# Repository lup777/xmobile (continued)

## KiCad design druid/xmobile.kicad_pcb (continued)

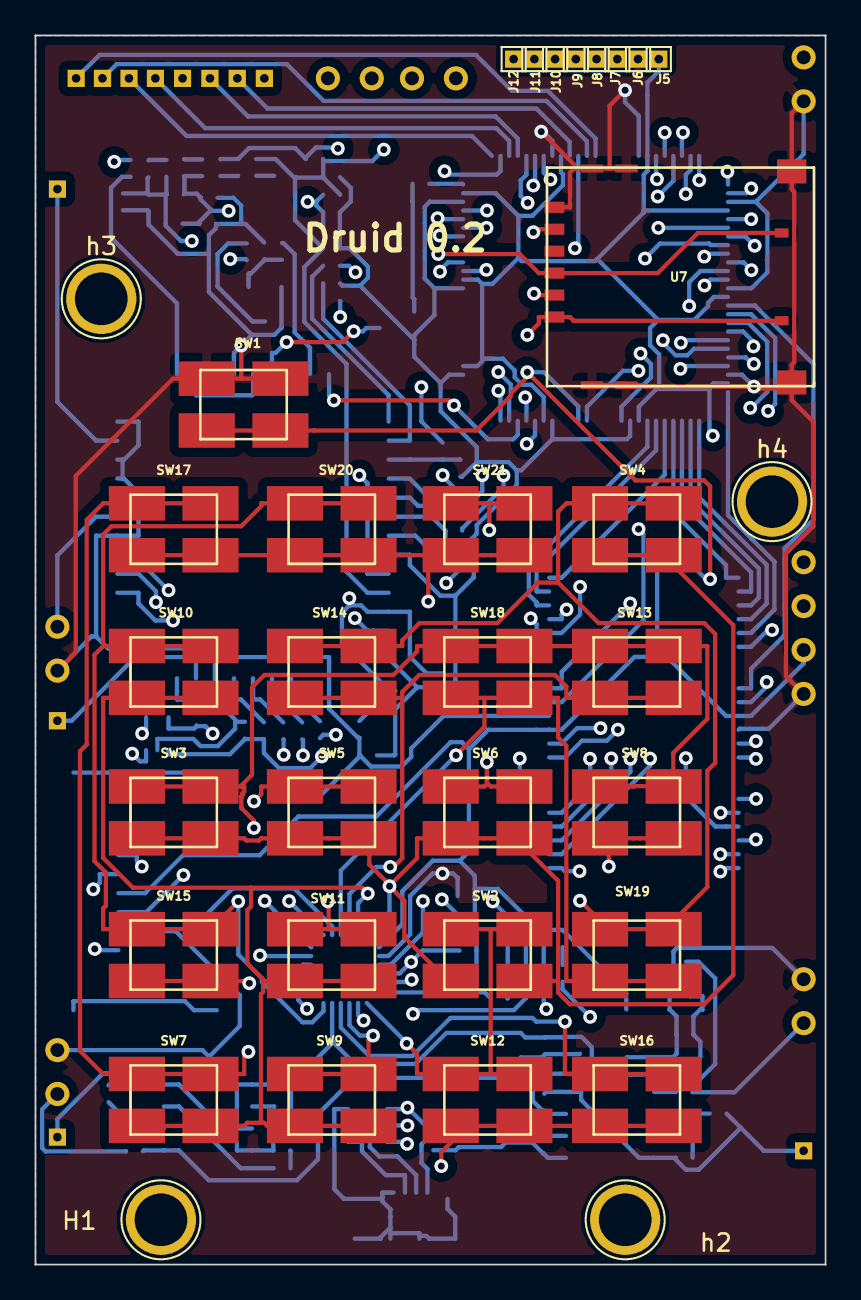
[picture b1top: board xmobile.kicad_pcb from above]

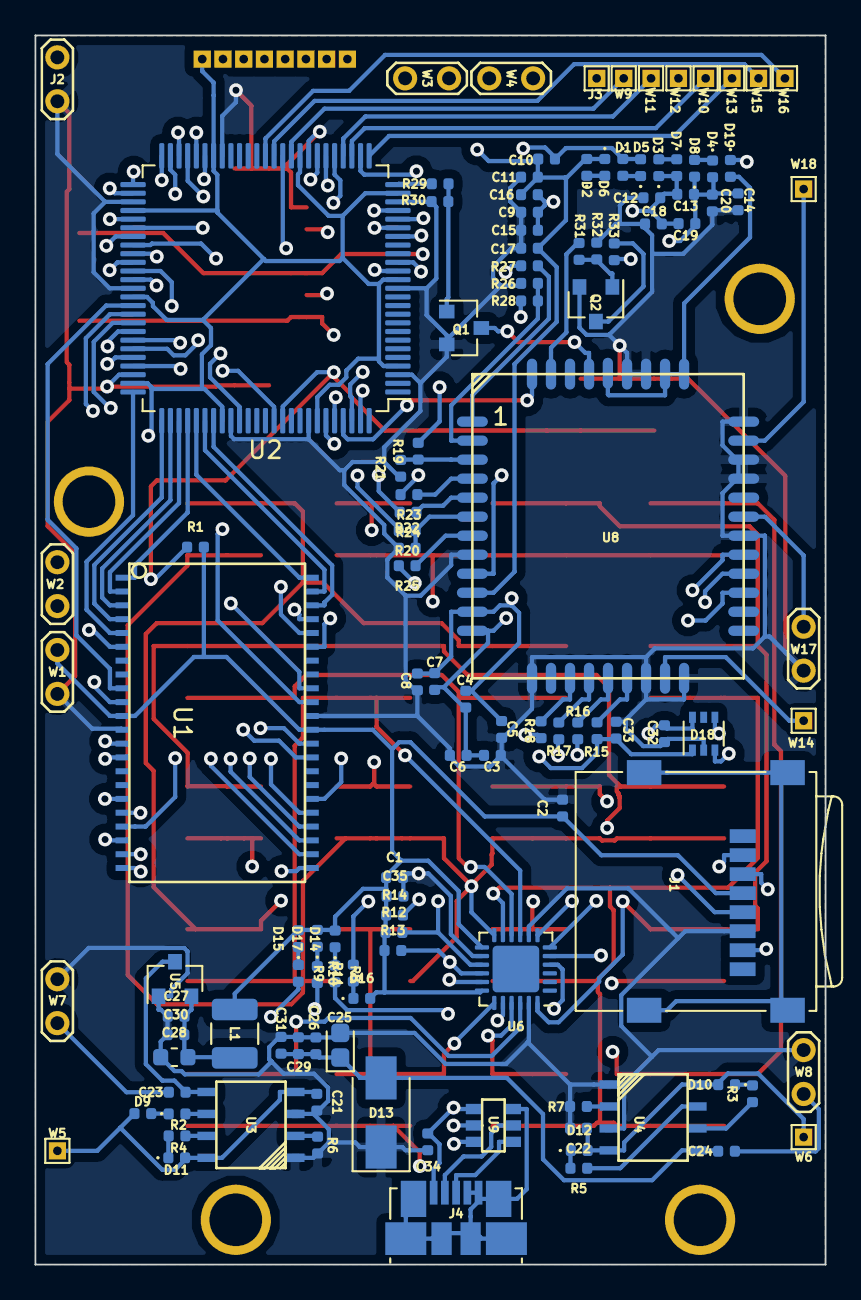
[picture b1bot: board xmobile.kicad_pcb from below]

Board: 4 copper layers, 45.7 x 71.1 mm, 154 parts (120 on the bottom side), 133 nets.

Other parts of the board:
H1: 1pin
J5, J6, J7, J8, J9, J10, J11, J12: EPD_1; TestPoint_THTPad_1.0x1.0mm_Drill0.5mm
h2, h3, h4: 1pin

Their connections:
3.3V: J5.1; also elsewhere on the board
/EPD_BUSY: J12.1; also elsewhere on the board
/EPD_CLK: J8.1; also elsewhere on the board
/EPD_CS: J9.1; also elsewhere on the board
/EPD_DC: J10.1; also elsewhere on the board
/EPD_DIN: J7.1; also elsewhere on the board
/EPD_RST: J11.1; also elsewhere on the board
GND: J6.1; also elsewhere on the board

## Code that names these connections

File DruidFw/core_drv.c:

// core_drv.c
#include <avr/io.h>

#include "global.h"

#include "core_drv.h"

void WriteEBI(uint32_t Address, uint8_t Val);
uint8_t ReadEBI(uint32_t Address);
void sram_read_enable(void);
void sram_write_enable(void);

inline void clk_init(void) {
    //OSC_PLLCTRL = 0x16;  // 2 * 16 = 32MGz
  OSC_CTRL = OSC_RC32MEN_bm;

  while( !( OSC_STATUS & OSC_RC32MRDY_bm ) ); // waite while 32MGXz osc ready

  CCP = CCP_IOREG_gc;
  CLK_CTRL = CLK_SCLKSEL_RC32M_gc;
}

void int_init(void) {
  //clear_global_interrupt();

    CCP = CCP_IOREG_gc;

    PMIC.CTRL = (PMIC_LOLVLEN_bm | PMIC_HILVLEN_bm);

    PMIC.INTPRI = 0x00;
}

inline void sram_write_enable(void) {
  /*PORTH.OUTSET =
    //| PIN1_bm   // OE
    //| PIN0_bm  // WE
    ;*/
  PORTH.OUTCLR =
    //| PIN1_bm   // OE
    PIN0_bm  // WE
    ;
}

inline void sram_read_enable(void) {
  PORTH.OUTSET =
    //| PIN1_bm   // OE
    PIN0_bm  // WE
    ;
  PORTH.OUTCLR =
    PIN1_bm   // OE
    //PIN0_bm  // WE
    ;
}

void sram_init(void) {
  /* EXAMPLE
    PORTCFG.EBIOUT = PORTCFG_EBIADROUT_PF_gc | PORTCFG_EBICSOUT_PH_gc;
    EBI.CTRL = EBI_SRMODE_NOALE_gc | EBI_IFMODE_4PORT_gc;

    EBI.CS2.BASEADDR = 0x0000;
    EBI.CS2.CTRLB = EBI_CS_SRWS_1CLK_gc;   // 62,5ns R/W cycle @ 32MHz - you have to meet your SRAM's speed specification
    EBI.CS2.CTRLA = EBI_CS_ASPACE_128KB_gc | EBI_CS_MODE_SRAM_gc;

  */

  // NEED PORT CONFIGURATION
  // PK - A0 .. A7
  // PF - A8 .. A15
  // PH - A16.. A19, CE1, CE2, OE, WE
  // PJ - D0 .. D7
  // PH2 - CE1
  // PH3 - CE2
  //   PH0 - WE
  //   PH1 - OE (RE)
  //   PH2 - CE1
  //   PH3 - CE2
  //   PH4 .. PH7 - A16 .. A19
  PORTK.DIRSET = 0xFF; // A0 .. A7
  PORTF.DIRSET = 0xFF; // A8 .. A15
  PORTH.DIRSET = 0xFF; // A16.. A19, CE1, CE2, OE, WE
  PORTJ.DIRCLR = 0xFF; // D0 .. D7

  PORTH.OUTSET =
    PIN4_bm | PIN6_bm | PIN6_bm | PIN7_bm // A16 - A19
    | PIN2_bm   // CE1
    | PIN3_bm   // CE2
    //| PIN1_bm   // OE
    //| PIN0_bm  // WE
    ;

  PORTH.OUTCLR =
    //PIN4_bm | PIN6_bm | PIN6_bm | PIN7_bm // (in real A18..A21) A16 - A19 
    //PIN2_bm   // CE1 (in real A16)
    //| PIN3_bm // CE2 (in real A17)
    PIN1_bm   // OE
    | PIN0_bm   // WE
    ;
  
  

  PORTCFG.EBIOUT = PORTCFG_EBIADROUT_PF_gc | PORTCFG_EBICSOUT_PH_gc;

  EBI.CTRL = EBI_SRMODE_NOALE_gc // do not use address multiplexing
    | EBI_IFMODE_4PORT_gc;       // 4 port mode. This mode reserved
                                 // IFMODE[1:0] = 1 0 (bits)

  //EBI.CS0.CTRLA = EBI_CS_MODE_DISABLED_gc;
  //EBI.CS1.CTRLA = EBI_CS_MODE_DISABLED_gc;
  //EBI.CS2.CTRLA = EBI_CS_MODE_DISABLED_gc;

  
  EBI.CS3.CTRLA = EBI_CS_ASPACE_128KB_gc  // size of the block above the base address
    | EBI_CS_MODE_SRAM_gc;              // SRAM mode

  EBI.CS3.CTRLB = EBI_CS_SRWS_1CLK_gc;  // One Clk per 2 cycles wait state

  // lowest a]ddress in the address space enabled by chip select
  //EBI.CS3.BASEADDR = (uint16_t)((0x100000 >> 8) & 0xFFFFF);
  //EBI.CS3.BASEADDR = (uint16_t)0x100000;
  EBI.CS3.BASEADDR = (uint16_t)0x0;
}


// 128KB: 0x0000 - 0x1F400
#ifndef DISABLE_LOGS
#if 0
bool check_sram(void) {
  volatile uint32_t ptr_start = 0x4000;
  volatile uint32_t ptr_end = 0x100000; // 128KB
  volatile uint32_t ptr;
  
  volatile uint8_t data = 0xAA;
  uint8_t step = 0xFF;
  bool result = true;;
  volatile uint8_t value;

  for (;ptr_start + step < ptr_end; ptr_start += step) {

    sram_write_enable();
    for (data = 0, ptr = ptr_start;
	 ptr <= ptr_start + step;
	 ptr++, data++) {
      WriteEBI(ptr, data);
      //_log("write: 0x%02X", data);
    }

    sram_read_enable();
    for (data = 0, ptr = ptr_start;
	 ptr <= ptr_start + step;
	 ptr++, data ++) {
      value = ReadEBI(ptr);
      //_log("read: 0x%02X", value);
      if (value != data) {
	uint16_t tmpl = (uint16_t)(ptr & 0xFFFF);
	uint16_t tmph = (uint16_t)(ptr >> 16) & 0xFFFF;
	_log("addr: 0x%04X%04X failed", tmph, tmpl);
	result = false;
	break;
      }
    }

    if (result == false) break;

    if (result == true) {
      uint16_t tmpl = (uint16_t)(ptr & 0xFFFF);
      uint16_t tmph = (uint16_t)(ptr >> 16) & 0xFFFF;

      _log("addr: 0x%04X%04X success", tmph, tmpl);
    }
  }

  _log("test done.");
  return true;
}
#else
bool check_sram(void) {
  volatile uint16_t ptr_start = 0x4000;
  volatile uint16_t ptr_end = 0xFFFF; // 128KB
  volatile uint16_t ptr;
  
  volatile uint8_t data = 0xAA;
  uint8_t step = 0xFF;
  bool result = true;;
  volatile uint8_t value;

  for (;ptr_start + step < ptr_end; ptr_start += step) {

    sram_write_enable();
    for (data = 0, ptr = ptr_start;
	 ptr <= ptr_start + step;
	 ptr++, data++) {
      //WriteEBI(ptr, data);
      *((uint16_t*)ptr) = data;
      //_log("write: 0x%02X", data);
    }

    sram_read_enable();
    for (data = 0, ptr = ptr_start;
	 ptr <= ptr_start + step;
	 ptr++, data ++) {
      //value = ReadEBI(ptr);
      value = *((uint16_t*)ptr);
      //_log("read: 0x%02X", value);
      if (value != data) {
	uint16_t tmpl = (uint16_t)(ptr & 0xFFFF);
	uint16_t tmph = 0;
	_log("addr: 0x%04X%04X failed", tmph, tmpl);
	result = false;
	break;
      }
    }

    if (result == false) break;

    if (result == true) {
      uint16_t tmpl = (uint16_t)(ptr & 0xFFFF);
      uint16_t tmph = 0;

      _log("addr: 0x%04X%04X success", tmph, tmpl);
    }
  }

  _log("test done.");
  return true;
}
#endif
#endif

uint8_t ReadEBI(uint32_t Address)
{
 uint8_t Seg = (uint8_t)(Address >> 16);
 uint16_t Off = (uint16_t)Address;
 uint8_t Value;
 __asm__ __volatile__
 (
   "in __tmp_reg__,%3"          "\n\t"  /* store RAMPZ */
   "out %3,%1"                  "\n\t"  /* load new RAMPZ */
   "ld %0,%a2"                  "\n\t"  /* load Ret */
   "out %3,__tmp_reg__"         "\n\t"  /* restore RAMPZ */
   :  "=&r" (Value)                     /* %0 */
   :  "r"   (Seg),                      /* %1 */
      "z"   (Off),                      /* a2 */
      "I"   _SFR_IO_ADDR(RAMPZ)         /* %3 */
  );

  return( Value );
}

void WriteEBI(uint32_t Address, uint8_t Val)
{
  uint8_t Seg = (uint8_t)(Address >>16);
  uint16_t Off = (uint16_t)Address;
 __asm__ __volatile__
 (
   "in __tmp_reg__,%3"          "\n\t"  /* store RAMPZ */
   "out %3,%1"                  "\n\t"  /* load new RAMPZ */
   "st %a2,%0"                  "\n\t"  /* write byte */
   "out %3,__tmp_reg__"         "\n\t"  /* restore RAMPZ */
   :
   :  "r"  (Val),                       /* %0 */
      "r"  (Seg),                       /* %1 */
      "z"  (Off),                       /* %2 (Z) */
      "I"  _SFR_IO_ADDR(RAMPZ)          /* %3 */
 );
}

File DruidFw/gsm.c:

// gsm.c

#include "gsm.h"

#include "FreeRTOS.h"
#include "task.h"
#include "message_buffer.h"

#include <string.h>
#include <avr/interrupt.h>

#include "global.h"
#include "spi.h"
#include "kbd2.h"
#include "task_mgr.h"

#define READ_BUFFER_SIZE 255

void GSM_CallCmd(const char* msg);
void gsm_sendcstr(char* str, uint8_t len);
bool GSM_SendByte(char c, uint16_t delay_ms);
bool GSM_ReadByte(char* out, uint16_t delay_ms);
char GSM_ReadResultCode(uint16_t delay_ms, char* out);
void gsm_send_cmd_end(void);

// new
void send_byte(char byte);

// http://codius.ru/articles/GSM_%D0%BC%D0%BE%D0%B4%D1%83%D0%BB%D1%8C_SIM800L_%D1%87%D0%B0%D1%81%D1%82%D1%8C_1

//char rbuf[READ_BUFFER_SIZE];
char gresult;

void GSM_Init(void) {
  //_log("GSM Start gsm init");
  // PA2 - status

  PORTD.DIRSET = PIN0_bm; // power key
  PORTD.OUTCLR = PIN0_bm; // power key

  vTaskDelay((TickType_t)(1000 / portTICK_PERIOD_MS));

  PORTD.OUTSET = PIN0_bm; // power key releas//PORTD.OUTCLR = PIN0_bm;

  //gsm_msg_buffer = xMessageBufferCreate( 10 );

  PORTA.DIRCLR = PIN2_bm; // status
  PORTD.DIRCLR = PIN1_bm; // RI
  
  PORTE.DIRCLR = PIN2_bm; // Rx
  PORTE.DIRSET = PIN3_bm; // Tx
  PORTE.DIRCLR = PIN0_bm; // PE0 RTS (open) request to send
  PORTD.DIRCLR = PIN4_bm; // CTS clear to send PD4
  PORTD.DIRCLR = PIN3_bm; // DTR data terminal ready PD3
  PORTD.DIRCLR = PIN2_bm; // DCD data carrier detect PD2
  

  USARTE0.CTRLC = USART_CMODE_ASYNCHRONOUS_gc | USART_PMODE_DISABLED_gc
    | USART_CHSIZE_8BIT_gc;

  USARTE0.CTRLA =
    USART_RXCINTLVL_LO_gc
    | USART_TXCINTLVL_OFF_gc
    | USART_DREINTLVL_OFF_gc;

  uint16_t bsel = 1047;// 1079;//68;
  uint8_t bscale = 6;//0;
  USARTE0.BAUDCTRLA = bsel & 0xff; // 115200  - 32MGz internal osc
  USARTE0.BAUDCTRLB =
    (bsel >> 8) | ((16 - bscale) << 4); // 115200  - 32MGz internal osc

  USARTE0.CTRLB = USART_TXEN_bm | USART_RXEN_bm /*| USART_CLK2X_bm | USART_TXB8_bm*/;

  _log("GSM init completed");
}

bool gsm_status(void) {
  return ((PORTA.IN & PIN2_bm) != 0);
}

void send_byte(char data) {
  while((USARTE0.STATUS & USART_DREIF_bm) == 0) {};
  USARTE0.DATA = data;
}

void gsm_send_str(char* data, size_t len) {
  gsm_send_str_ne(data, len);
  gsm_send_cmd_end();
}
void gsm_send_str_ne(char* data, size_t len) {
  size_t i = 0;

  for(; i < len; i++) {
    send_byte(data[i]);
  }
}
void gsm_send_cstr(const char* data) {
  _log("gsm -> %s", data);
  gsm_send_str((char*)data, strlen(data));
}

void gsm_send_cstr_ne(const char* data) {
  gsm_send_str_ne((char*)data, strlen(data));
}

void gsm_send_cmd_end(void) {
  send_byte('\r');
  send_byte('\n');
}

ISR(USARTE0_TXC_vect) {
}

ISR(USARTE0_RXC_vect) {
  unsigned char data;
  BaseType_t need_yeld = pdFALSE;
  static unsigned char buffer[50];
  static int idx = 1;

  buffer[idx] = USARTE0.DATA;
  data = USARTE0.DATA;

  while((USARTE1.STATUS & USART_DREIF_bm) == 0) {};
  USARTE1_DATA = data;
  
  if (idx >= 50)
    idx = 1;
  
  buffer[idx] = data;

  if ((buffer[idx] != '\r') && (buffer[idx] != '\n')) {
    idx++;
  } else {
    if (idx > 2) {
      buffer[0] = MSG_HEADER_GSM;
      xMessageBufferSendFromISR(tm_msg_buf_handle,
				buffer,
				idx,
				&need_yeld);
      idx = 1;
    }
  }

  if (need_yeld == pdTRUE)
    taskYIELD();
}

// Responce format: "\r\n<responce>\r\n"

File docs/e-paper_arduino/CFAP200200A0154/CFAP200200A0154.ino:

//=============================================================================
// "Arduino" example program for Crystalfontz ePaper. 
//
// This project is for the CFAP200200A0-0154 :
//
//   https://www.crystalfontz.com/product/cfap200200a00154
//
// It was written against a Seeduino v4.2 @3.3v. An Arduino UNO modified to
// operate at 3.3v shoudl also work.
//-----------------------------------------------------------------------------
// This is free and unencumbered software released into the public domain.
// 
// Anyone is free to copy, modify, publish, use, compile, sell, or
// distribute this software, either in source code form or as a compiled
// binary, for any purpose, commercial or non-commercial, and by any
// means.
// 
// In jurisdictions that recognize copyright laws, the author or authors
// of this software dedicate any and all copyright interest in the
// software to the public domain. We make this dedication for the benefit
// of the public at large and to the detriment of our heirs and
// successors. We intend this dedication to be an overt act of
// relinquishment in perpetuity of all present and future rights to this
// software under copyright law.
// 
// THE SOFTWARE IS PROVIDED "AS IS", WITHOUT WARRANTY OF ANY KIND,
// EXPRESS OR IMPLIED, INCLUDING BUT NOT LIMITED TO THE WARRANTIES OF
// MERCHANTABILITY, FITNESS FOR A PARTICULAR PURPOSE AND NONINFRINGEMENT.
// IN NO EVENT SHALL THE AUTHORS BE LIABLE FOR ANY CLAIM, DAMAGES OR
// OTHER LIABILITY, WHETHER IN AN ACTION OF CONTRACT, TORT OR OTHERWISE,
// ARISING FROM, OUT OF OR IN CONNECTION WITH THE SOFTWARE OR THE USE OR
// OTHER DEALINGS IN THE SOFTWARE.
// 
// For more information, please refer to <http://unlicense.org/>
//=============================================================================
// The display is SPI, include the library header.
#include <SPI.h>

// Include the ePaper module header.
#include "ePaper_CFAP200200A0154.h"

// Include the images. These images were prepared with "bmp_to_epaper" which
// is available on the Crystalfontz site.
#include "Images_for_CFAP200200A00154.h"
// This module is 200x200 pixels. Make sure that the image files make sense.
#if ((HEIGHT_PIXELS != (200)) || (WIDTH_PIXELS  != (200)))
#error "IMAGE INCLUDE FILE IS WRONG SIZE"
#endif
//=============================================================================
void Partial_Update_Letters_Demo(void)
  {
  Load_LUT_For_Partial_Update();
  ePaper_POWERON();

  //Fill entire display RAM with background image.
  SetDisplayArea(0,                  // X start
                 WIDTH_MONO_BYTES-1, // X end
                 HEIGHT_PIXELS-1,    // Y start
                 0);                 // Y end
  Load_Flash_Image_To_Display_RAM(WIDTH_PIXELS,  //X size
                                  HEIGHT_PIXELS, //Y size
                                  Mono_1BPP);    //Image
  
  //Swap foreground and background, this will
  //show the full-screen image we just put up.
  ePaper_Update_Partial();

  //Now again fill entire display RAM with the same
  //background image. This will make it so the parts
  //of the dispaly that are not changed by the partial
  //update do not flicker.
  //If you instead load Diag_1BPP, you can see the
  //background swap out on every other update.
  SetDisplayArea(0,                  // X start
                 WIDTH_MONO_BYTES-1, // X end
                 HEIGHT_PIXELS-1,    // Y start
                 0);                 // Y end
  Load_Flash_Image_To_Display_RAM(WIDTH_PIXELS,  //X size
                                  HEIGHT_PIXELS, //Y size
                                  Mono_1BPP);    //Image

  // Now we can animate some smaller bitmaps to show
  // the four letters 'C' 'F' 'A' 'P' 
  uint8_t
    i;
  for(i=0;i<12;i++)
    {
    //Partial write to background
    SetDisplayArea(6,                             // X start
                   6+LETTER_WIDTH_MONO_BYTES-1,   // X end
                   126,                           // Y start 
                   126-(LETTER_HEIGHT_PIXELS-1)); // Y end
    switch(i%4)
      {
      case 0:
        Load_Flash_Image_To_Display_RAM(LETTER_WIDTH_PIXELS,
                                        LETTER_HEIGHT_PIXELS,
                                        (uint8_t *)Mono_Letter_C);
        break;
      case 1:
        Load_Flash_Image_To_Display_RAM(LETTER_WIDTH_PIXELS,
                                        LETTER_HEIGHT_PIXELS,
                                        (uint8_t *)Mono_Letter_F);
        break;
      case 2:
        Load_Flash_Image_To_Display_RAM(LETTER_WIDTH_PIXELS,
                                        LETTER_HEIGHT_PIXELS,
                                        (uint8_t *)Mono_Letter_A);
        break;
      case 3:
        Load_Flash_Image_To_Display_RAM(LETTER_WIDTH_PIXELS,
                                        LETTER_HEIGHT_PIXELS,
                                        (uint8_t *)Mono_Letter_P);
        break;
      }
    ePaper_Update_Partial();
    delay(100);
    }
  ePaper_POWEROFF();
  }
//===========================================================================
void setup(void)
  {
  //Debug port / Arduino Serial Monitor
  Serial.begin(115200);
  
  // Configure the pin directions
  pinMode(EPD_BUSY, INPUT);
  pinMode(EPD_RESET , OUTPUT);   
  pinMode(EPD_CS, OUTPUT);     
  pinMode(EPD_DC, OUTPUT);     
  pinMode(EPD_BUSSEL, OUTPUT);
  // Set output pins' default state
  digitalWrite(EPD_RESET, HIGH);   //active low
  digitalWrite(EPD_CS, HIGH);      //active low
  digitalWrite(EPD_DC, HIGH);      //active low 
  digitalWrite(EPD_BUSSEL, LOW);   // 4 wire mode
  
  //Set up SPI interface
  SPI.beginTransaction(SPISettings(500000, MSBFIRST, SPI_MODE0));
  SPI.begin();
  //Initialize the display controller hardware 
  ePaper_Init();
  }
//=============================================================================
void loop()
  {
  // Show the logo from Images_for_CFAP200200A00154.h
  Show_Full_Screen_Image(Mono_1BPP,      //image data
                         WIDTH_PIXELS,   //X size
                         HEIGHT_PIXELS); //Y size
  delay(3000);

  //Loop through some smaller images to show off the partial update feature.
  Partial_Update_Letters_Demo();
  delay(2500);
  }
//=============================================================================

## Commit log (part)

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2017-12-02 1. Работает вывод произвольных срок на экран. 2. Руссике и английские шрифты работают в koi8-r в нижнем регистре 3. Некоторые другие символы доступны также. 4. Всё это проверено на Arduino UNO. Памят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
2017-12-02 Переименован файл скетча чтобы он собирался в дуино студии
2017-12-02 удалён ненужный e-paper-test.ino
2017-12-08 added port of FreeRTOS for Amega328p. It compiles, but working was not checked.
2017-12-09 Добавлен простой GSM тест для ардуины, который просо передаёт сообщения с терминала в модуль и обратно. добавлен white_screen.h
2017-12-09 две задачи моргают лампочками
2017-12-10 Написан таск для отправки байтов по USART0. Просто посылает байт 'a' постоянно и ждёт пока не закончится передача. Код написан, работоспособность не проверялась ни разу. Компилируется без ошибок. ЗЫ: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
2017-12-10 USART работает на скорости 9600, проверено с ардуиной мега на Serial1.
2017-12-10 Теперь USART нормальное работает. Реализована дебажная задача передающая строки из очереди в уарт. Для проверки на другой строне использовалась вторая ардуина передающая в компьютер.
2017-12-10 Написана таска для отправки данных по SPI. Пока не компилится. Не проверено.
2017-12-11 Теперь SPI работает на отправку данных. Проверено с ардуиной в SPI slave режиме.
2017-12-12 Добавлен параметр компиляции -Werror Заменены очереди на буферные потоки. Не проверено.
2017-12-12 Начало портирования логики работы с экраном.
2017-12-13 Функции логики для работы с экраном портированы, но проверены. Написана простоя таска для экрана, в ней только инициализация (тоже не проверена).
2017-12-13 Добавлено обновление фоновой картинки на дисплее каждые 5 секунд. Работа экрана вообще не проверялась.
2018-02-10 нормально работает dbg(char* frmat, ...) с UART-USB переходником Далее будет пытаться подключить 4.2 дисплей
2018-03-24 Последня версия схемы. - Электрическая схема закончена. - Корпуса компонентов установлены не все. Надобы выбрать резитсоры по-больше (вместо 0402)
2018-03-24 - Переделана клавиатура - установлены все корпуса микросхем
2018-03-25 Добавлен список цепей
2018-03-25 Добавлен TQFP44 корпус для XMega
2018-03-31 Теперь все площадки разложены по кучкам
2018-03-31 Заменил посадочные места для некоторых контактных расчёсок
2018-04-01 зменена посадочная площадка (меньше чем была) лоя кондернасоторв 100n
2018-04-08 Всё разведено кроме земель. Площидки надо проверять.
2018-10-13 Ground lines and poligones are completed.
2018-10-18 Added board borders on Edge.cuts layer. Added size of board. Created Gerber files (and sent to https://jlcpcb.com for manufacturing)
2018-11-12 [Druid] Fix repo issues Remove submodule
2018-11-15 added missing heap sources. add code for e-paper, but not working
2018-11-17 e-paper full update works fine. partial update not implemened.
2018-11-18 Keyboard code completed, but not tested, not all buttons has completed.
2018-11-19 add TODO and test folder
2018-11-19 Created UI thread. Use critical senction to send pressed key info to UI thread (works only once) Maybe replace critical sections by mutexes. Added global.h Keyboard works ok, but there are false alar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
2018-11-20 Add fonts.c/h. Add function for getting picture by char code. Use in in UI thread for testing.
2018-11-20 Use queues in logs. Use binary semaphore in UI. EPS_ShowPartialImages works not stable.
2018-11-22 [KBD] Reworked KBD reading and checking. [UI] Added function EPD_SHowString()
2018-11-23 [UI] Remove EPD init from main thread (in UI thread remains). [KBD] Added test. KBD Should work 0_o
2018-11-23 [LOG] log() renamed to _log() to avoide conflict with avr log (nath). [MAKE] Remove warnings, enable werror
2018-11-23 [MAKE] Add clean to default make target
2018-11-23 [LOG] Complete _clog() function. Was not tested.
2018-11-23 [EPD] Wrap partial update code into critical section. Warks batter. [FONT] EPD_ShowString now can print english strings. [LOG] Output uint8_t and uint16_t in logs.
2018-11-24 [TEL] Telephone app moved to separate file. [EPD] Added EPS_StartPartial, EPD_StopPartial and EPD_ContinuePartial() functions for partial update.
2018-11-24 [EPD] Move epd init into main thread and disable UI thread. [KBD] Fix key codes on kbd
2018-11-25 [GSM] Add gsm module, init works ok. [APP] Use dynamic memory alloc to test [MAKE] Heap_4.c activated
2018-11-26 [MENU] menu structure replaced fromthread to global space.
2018-11-27 [GSM] Start to write ReadByte with timeout [TODO] added some notes
2018-11-28 [GSM] Some functions to work with gsm
2018-11-29 [APP][MENU] menu app rewritted to use message pump [LOG] usart now uses rx isr to emulate kbd key press and sends messages to applications
2018-11-29 [LOG] Check APP message buffer handler for NULL
2018-11-29 [TEL] rewrite telephone to use message pump
2018-11-30 [EPD] split spi and epd. Need to test telephone app. remove two calls of critical section.
2018-11-30 [TEL] Add close app functionality
2018-12-02 [MAKE] fix issue with programming in Linux
2018-12-03 [USART] Add flow control to GSM ISR (CTS)
2018-12-03 [APP] Put all calls of MessageBufferSendinto critical senction. Small changes in mailbox id storing
2018-12-03 [USART][GSM][MENU] Send by TX interrupt with stream buffers. [APP] Apps do not works now :)
2018-12-04 continue investigation
2018-12-06 [SPI][EPD] Finish moving spi to interrupt driven tx/rx. Not tested.
2018-12-06 [USART][SPI] Add broadcast event messaging
2018-12-09 [EPD][SPI] SPI tx works using interrupt. EPD works. crash when pressing kbd key.
2018-12-10 [SPI] Use mutex while sending data via SPI [USART] Add SendMsg macro
2018-12-10 [GSM] Use SendMsg macro in gsm usart tx isr Fix missprint USARTD0_DATA -> USARTE0_DATA [APP] Add HANDLE == NULL check in SendMsg macro
2018-12-10 [APP] Added endian test
2018-12-10 [EPD][SPI] Some improvements. Now EPD works, but there is a huge timeout before menu show [LOG] Use "buffer empty" IRSin logs. Now it works well.
2018-12-12 [HW] Add SRAM component library
2018-12-12 [KBD] KBD works not good. key down works, key up works one than stuck.
2018-12-19 [XMEGA] Add BGA xmega electrical lib, SRAM connected (no power capacitors)
2018-12-23 [APP] Enable Telephone. Waork not ok
2019-01-21 Add 6 pin SIM holder (add pdf) Connect SIM800C to sim holder
2019-01-22 Design and connect GSM module.
2019-01-25 Connected GSM status pin to xmega added 4 LEDs to KBD contorller (PWM) EPD moved to USART (SPI mode)
2019-01-27 Added microSD slot.
2019-01-28 Add xmega pcb, Add SIM800 pcb Add SRAM pcb, Start to draw sim card holder pcb
2019-01-29 Old buttons replaced by membran buttons (electic and pcb) Added pcb for MAX7370 Cleared PCBs of resistor, capacitors and diodes
2019-01-29 Change PDI connector.
2019-02-18 Add TP4056 buttary charger (schema and pcb)
2019-02-19 Bat connectors replaced by test points
2019-02-19 Add some packages
2019-02-20 Added footprints for some elments in power module
2019-02-21 Add packages: power module completed. Add packages: keyboard module completed.
2019-02-21 move to kicad 5
2019-02-22 remove electric warnings and errors. annotate elements. fix microUSB-B symbol.
2019-02-22 Some small fixes. generated net list.
2019-02-24 fix U1 package pin names
2019-02-26 place components in rectangle.
2019-02-26 KBD controller and SRAM packages changed from BGA to ... TSOP and TQFN XMEGA packaged need to be changed
2019-02-27 Done with packages. Start to place components.
2019-02-28 Route completed. 149 vias.
2019-02-28 Added filled zones
2019-03-01 fix pcb issues.board completed.
2019-03-26 Increase CPU speed up to 32MGz. Now display speed is ok.
2019-03-27 added char renderer test in QT creator. works fine.
2019-03-27 Add RenderLine and RenderDot
2019-03-27 Add rendering zone
2019-03-27 Add RenderCircle and zoom. Need to add RenderSubBuffer (instead of RenderChar)
2019-03-28 fix red zone zoom
2019-03-28 fix left columt drawing. add RenderRectangle
2019-03-28 added RenderSubBuffer
2019-03-29 perform optimisations
2019-03-29 try t make RebderSubbuffer. works bad
2019-03-29 RenderSubBuffer completed.
2019-03-30 bug fixes. all ok, but need to simplifi rectangle drawing
2019-03-30 Simplify circles rendering
2019-03-31 Add rendering to FW
2019-04-02 added: edit buffer
2019-04-02 fixes
2019-04-02 small fixes. But there is crash when resizing buffer to the same size
2019-04-02 render zone is somethis about ok
2019-04-03 [QT render test] added automate scrolling while zooming
2019-04-03 Small fix of red zone.
2019-05-05 Debug USART ported to USARTE1 (from F0) also: - Display works (renderer) - debug works
2019-05-07 added kbd driver(MAX7370) not tested
2019-05-12 Added message box for kbd key kodes
2019-05-12 added gsm init. but not tested
2019-05-12 add message buffer for GSM rx
2019-05-13 minor code reorganisation
2019-05-13 remove new line from gsm responce
2019-05-13 add ebi 4 port docs and example
2019-05-19 dd simple telephone app. It can do voice call.
2019-05-19 add frame around phone number.
2019-05-20 Added some comments to core_drv.c related to SRAM. Added 2 examples of SRAM config
2019-05-21 check task creation result
2019-05-21 set \r and \n in right order in gsm ISR
2019-05-21 Add TextEdit object
2019-05-21 fix build error related to dynamix allocaion of TextEdit
2019-05-21 Add TextEdit_clear
2019-05-21 check TextEdit init status in main
2019-05-21 small fixes. does not work
2019-05-21 log stream replaced by queue. now works
2019-05-22 CHECK macro, EBI_CS_ASPACE(SIZE)_1KB_gc
2019-05-22 added MlineTextEdit
2019-05-22 Text editors improvements and comments fro port.c
2019-05-26 render font 12x22 bits. works, but picture should be mirrored
2019-05-27 added fonts of variable size (no code)
2019-05-27 fonts ready
2019-05-29 add AT protocol handler
2019-05-31 many changed. stack owerflow detection. All works now.
2019-06-01 try to catch RDY. something strange happend. GSB rebooted, zeroes instead of const strings
2019-06-01 remove display clearing in partial update
2019-06-01 fix telephone white screen
2019-06-02 code clean for epd and spi
2019-06-05 checge encoding on task mg and fonts. use koi8-r for ru strings
2019-06-05 add fonts to ui functions
2019-06-05 clean display
2019-06-12 all works. problems with gsm responce after sending a command.
2019-08-08 Add docker with avr toolchain. how to: 1. build: ./build_docker.sh 2. start: ./run_docker.sh 3. clearly stop: docker rm docker-avr 4. attach: docker start docker-avr && docker attach docker-avr
2019-08-08 create simple test fw
2019-09-23 EBI test works for 128KB memory config
2019-09-23 SRAM works but only 64kB (128KB in config). Looks like lines A16 - A19 (port H) do not work.
2019-09-25 initialise task handlers with NULL. Now 3 task works
2019-09-30 make menu in address book. And make call to telephone.
2019-10-01 Add menu for address book. Not checked.
2019-10-02 make call from address book successfully
2019-10-06 Add SDcard driver. Init works some times )
2019-10-07 Init of current SD completed. Read block 512b completed.
2019-10-09 Add some ext2 definitions
2019-10-10 super block found
2019-10-10 continue...
2019-10-12 read root dir successfully
2019-10-13 not working. start to make API for SD
2019-10-15 ext2 driver chapter 2. Open path works.
2019-10-15 correct file types
2019-10-16 sram optimisations in ext2 driver
2019-10-16 read multibloks files files (inderect block not supported)
2019-10-17 reading of singly inderect block pointer ok
2019-10-17 start to read doubly inderect blocks
2019-10-18 commment some logs
2019-10-22 Add tests to makefile
2019-10-22 New menu is working with address book.
2019-10-23 Read address book from SD card
2019-10-23 Addres book read test
2019-10-23 address book updated. read_file2 now retun 0 if file ended.
2020-04-04 add webgl case back part
2020-04-09 Fix show_hex(). Make buffer[] available in sander_ext2.c under SANDER define.
2020-04-10 fixed singly idndirect blocks read. Now it implemeted i read_file3 func.
2020-04-11 Fixes for read_file3() Test for read_file3() Triply indirect read not supported (no need for xmobile)
2020-04-11 Add new feature. functions to enumerate entries in directory (by inode num)
